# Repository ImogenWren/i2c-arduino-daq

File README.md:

# i2c Sensor Breakout Board for Data Aquisition Tasks
Flexible system for gathering i2c sensor data and providing sources to Data Aquisition software (LabVIEW, Python, Matlab, Terra Term, etc)

_The included firmware shows how to wrap up any external sensor library into a flexible format that allows easy modification to existing system and easy addition of 
new sensors._

_PCB Developed for use with Senserion i2c sensors, though is compatable with any i2c enabled periferal devices_

- Data output in CSV format over USB Serial connection as MVP for communications or logging with external software
- Could be improved by the addition of ModBus or JSON formatted data communication with error checking

## PCB

## Hardware Required
- Arduino Nano (PCB designed for this footprint, but other Arduino boards are compatable)
	- SDA A4
	- SCL A5
	
- DAQ (Data AQuisition) PCB
- Logging software
- USB port

## Sensirion SCD41 - CO2 Sensor - i2c
 - 5v or 3.3v

## Sensirion SEK-STC31 - CO2 Sensor - i2c

- 5v or 3.3v (calibrated for 3.3v)

 - Pinout: 
	- Vdd: brown    green
	- SCL: green    brown
	- GND: pink 	pink
	- SDA: yellow	Yellow
 
# Everything LabView

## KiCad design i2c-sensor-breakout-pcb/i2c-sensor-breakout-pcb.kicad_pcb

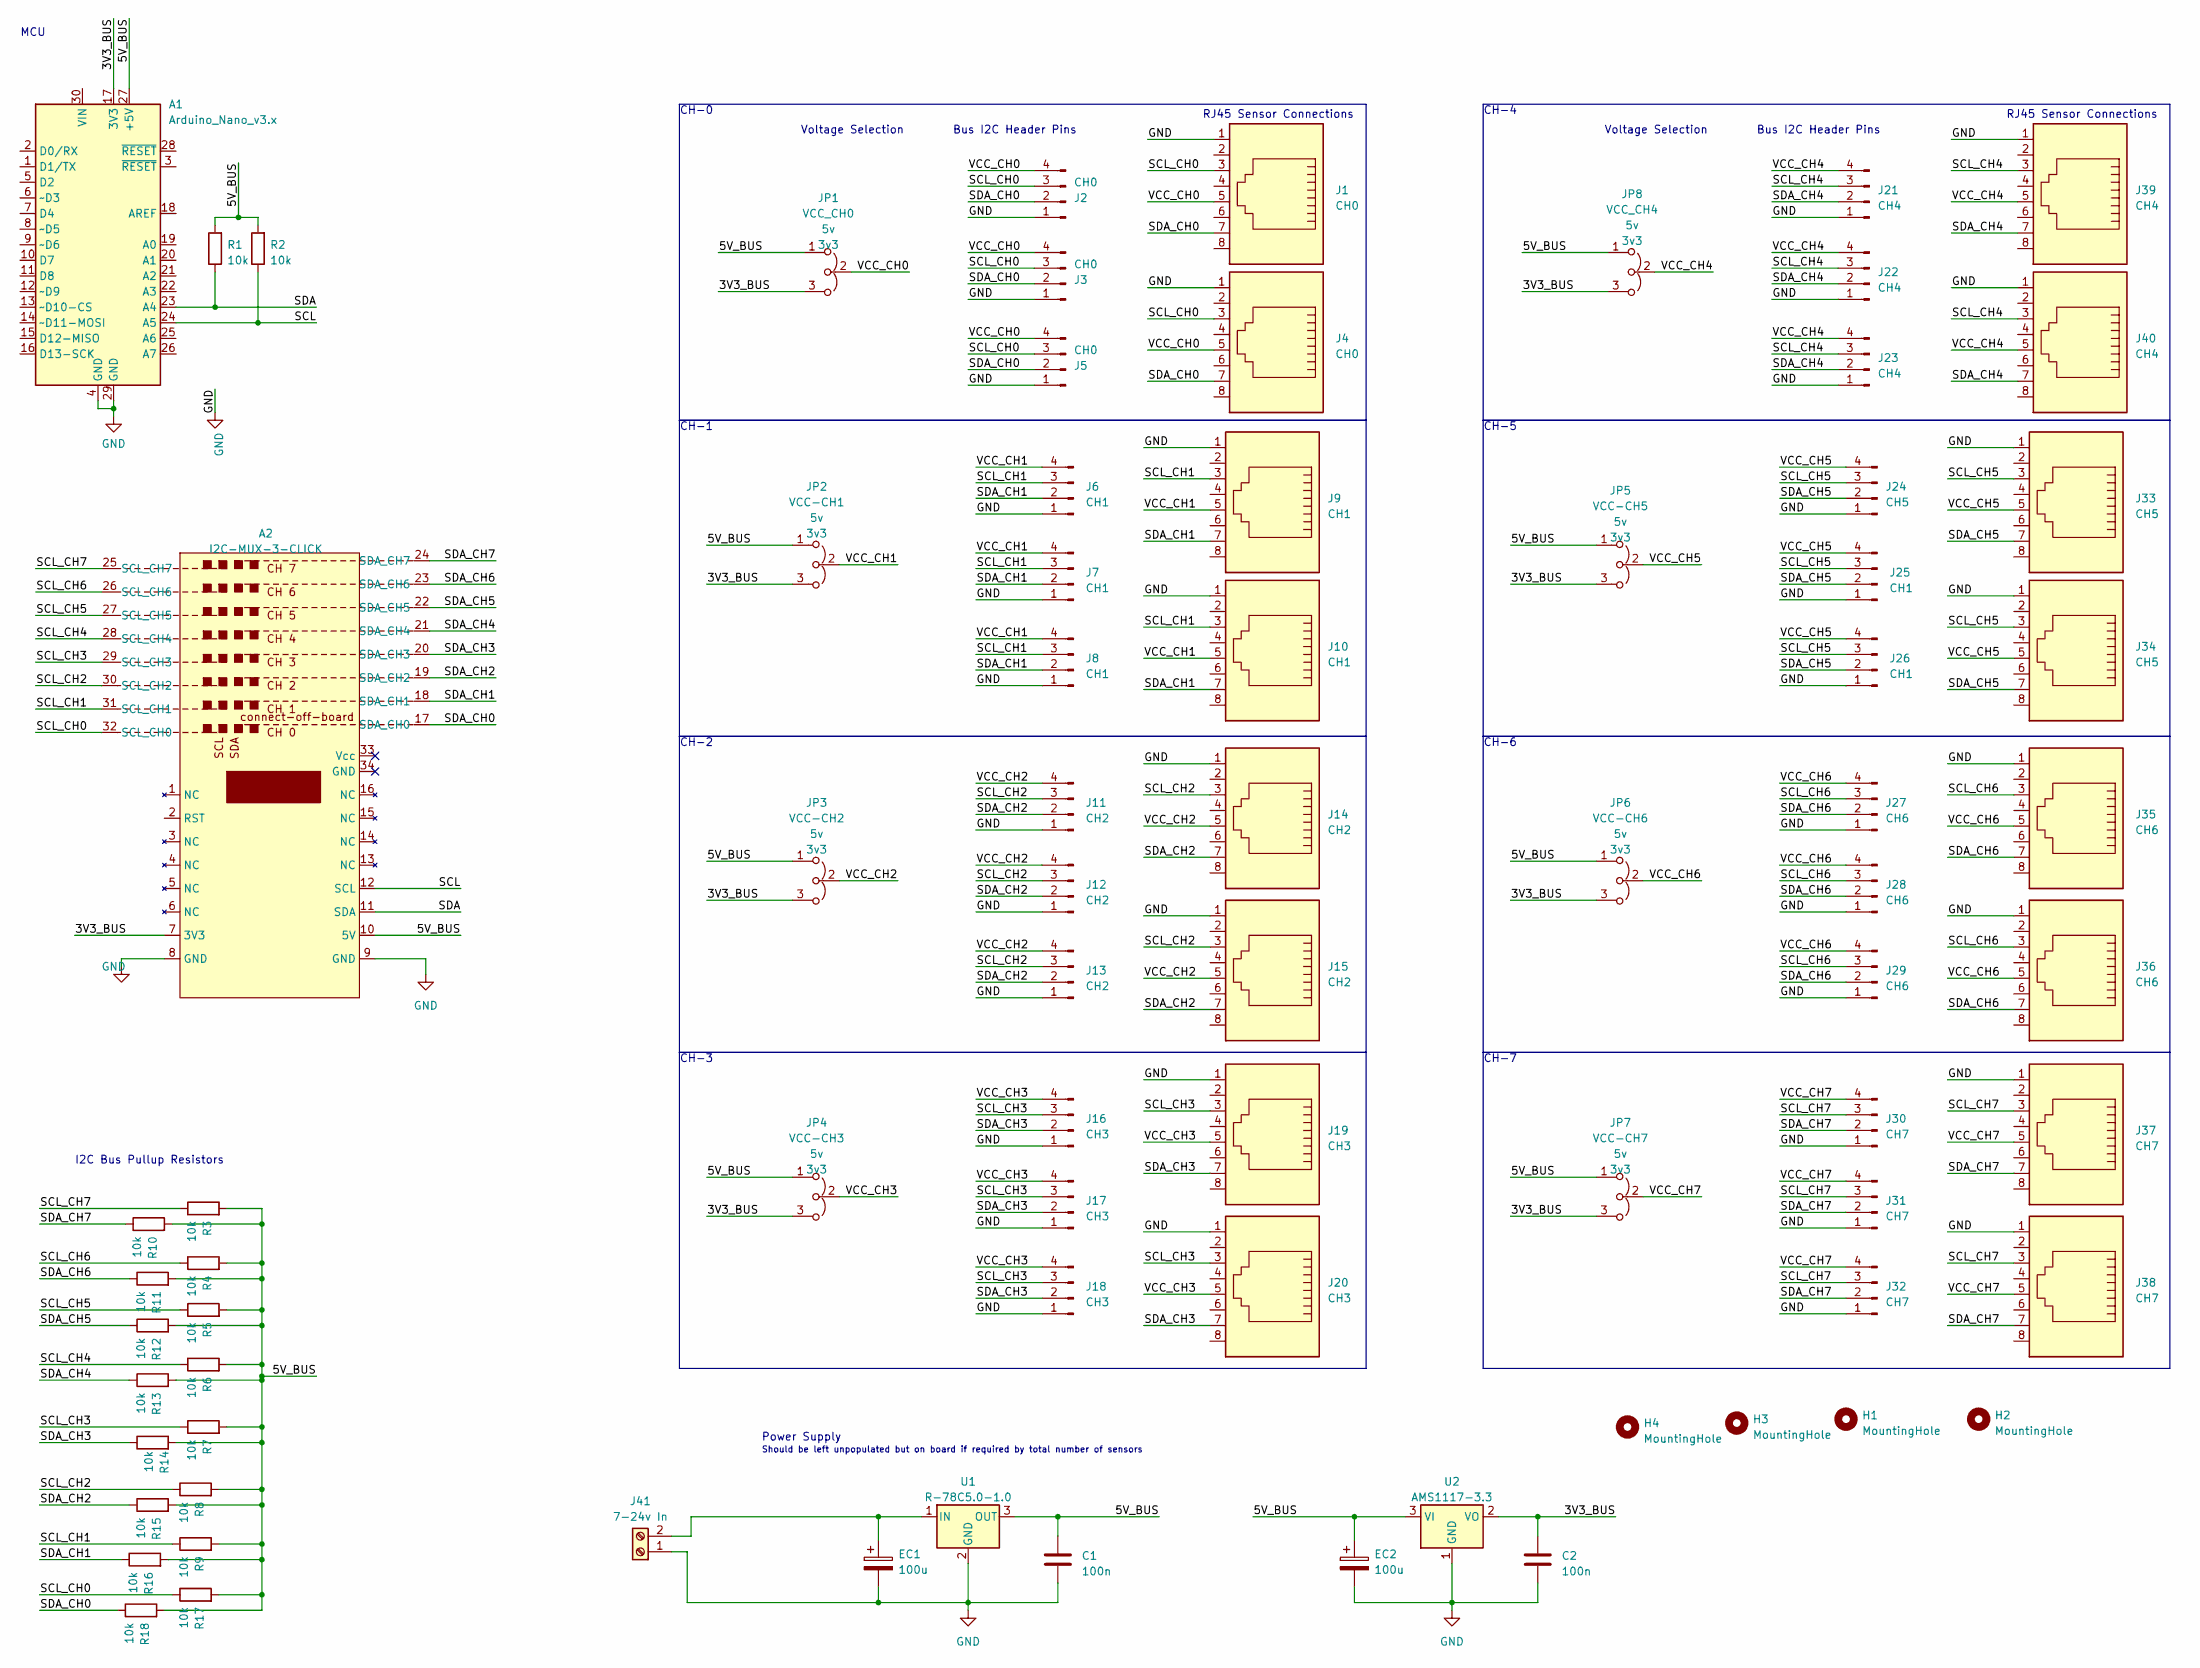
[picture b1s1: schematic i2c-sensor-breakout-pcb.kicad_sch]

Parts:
A1: Arduino_Nano_v3.x; Arduino_Nano
A2: I2C-MUX-3-CLICK
C1, C2: 100n; C_0805_2012_HandSolder_kawaii; JLCpart C779975
EC1, EC2: 100u; CP_Elec_10x10
H1, H2, H3, H4: MountingHole; MountingHole_3.2mm_M3_Pad_Via
J1, J4: CH0; RJ45_OST_PJ012-8P8CX_Vertical
J2, J3, J5: CH0; PinHeader_1x04_P2.54mm_Vertical
J6, J7, J8, J25, J26: CH1; PinHeader_1x04_P2.54mm_Vertical
J9, J10: CH1; RJ45_OST_PJ012-8P8CX_Vertical
J11, J12, J13: CH2; PinHeader_1x04_P2.54mm_Vertical
J14, J15: CH2; RJ45_OST_PJ012-8P8CX_Vertical
J16, J17, J18: CH3; PinHeader_1x04_P2.54mm_Vertical
J19, J20: CH3; RJ45_OST_PJ012-8P8CX_Vertical
J21, J22, J23: CH4; PinHeader_1x04_P2.54mm_Vertical
J24: CH5; PinHeader_1x04_P2.54mm_Vertical
J27, J28, J29: CH6; PinHeader_1x04_P2.54mm_Vertical
J30, J31, J32: CH7; PinHeader_1x04_P2.54mm_Vertical
J33, J34: CH5; RJ45_OST_PJ012-8P8CX_Vertical
J35, J36: CH6; RJ45_OST_PJ012-8P8CX_Vertical
J37, J38: CH7; RJ45_OST_PJ012-8P8CX_Vertical
J39, J40: CH4; RJ45_OST_PJ012-8P8CX_Vertical
J41: 7-24v In; TerminalBlock_Altech_AK300-2_P5.00mm; JLCpart C918120
JP1: VCC_CH0; SolderJumper-3-open-high-power
JP2: VCC-CH1; SolderJumper-3-open-high-power
JP3: VCC-CH2; SolderJumper-3-open-high-power
JP4: VCC-CH3; SolderJumper-3-open-high-power
JP5: VCC-CH5; SolderJumper-3-open-high-power
JP6: VCC-CH6; SolderJumper-3-open-high-power
JP7: VCC-CH7; SolderJumper-3-open-high-power
JP8: VCC_CH4; SolderJumper-3-open-high-power
R1, R2, R3, R4, R5, R6, R7, R8, R9, R10, R11, R12, R13, R14, R15, R16, R17, R18: 10k; R_0805_2012Metric_Pad1.20x1.40mm_HandSolder; JLCpart C2930231
U1: R-78C5.0-1.0; Converter_DCDC_RECOM_R-78E-0.5_THT
U2: AMS1117-3.3; SOT-223-3_TabPin2; JLCpart C2992570

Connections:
/3V3_BUS: A1.17 (3V3), A2.7 (3V3), C2.1, JP1.3 (B), JP2.3 (B), JP3.3 (B), JP4.3 (B), JP5.3 (B), JP6.3 (B), JP7.3 (B), JP8.3 (B), U2.2 (VO)
/5V_BUS: A1.27 (+5V), A2.10 (5V), C1.1, EC2.1, JP1.1 (A), JP2.1 (A), JP3.1 (A), JP4.1 (A), JP5.1 (A), JP6.1 (A), JP7.1 (A), JP8.1 (A), R1.2, R2.2, R3.2, R4.2, R5.2, R6.2, R7.2, R8.2, R9.2, R10.2, R11.2, R12.2, R13.2, R14.2, R15.2, R16.2, R17.2, R18.2, U1.3 (OUT), U2.3 (VI)
/SCL: A1.24 (A5), A2.12 (SCL), R2.1
/SCL_CH0: A2.32 (SCL_CH0), J1.3, J2.3, J3.3, J4.3, J5.3, R17.1
/SCL_CH1: A2.31 (SCL_CH1), J6.3, J7.3, J8.3, J9.3, J10.3, R9.1
/SCL_CH2: A2.30 (SCL_CH2), J11.3, J12.3, J13.3, J14.3, J15.3, R8.1
/SCL_CH3: A2.29 (SCL_CH3), J16.3, J17.3, J18.3, J19.3, J20.3, R7.1
/SCL_CH4: A2.28 (SCL_CH4), J21.3, J22.3, J23.3, J39.3, J40.3, R6.1
/SCL_CH5: A2.27 (SCL_CH5), J24.3, J25.3, J26.3, J33.3, J34.3, R5.1
/SCL_CH6: A2.26 (SCL_CH6), J27.3, J28.3, J29.3, J35.3, J36.3, R4.1
/SCL_CH7: A2.25 (SCL_CH7), J30.3, J31.3, J32.3, J37.3, J38.3, R3.1
/SDA: A1.23 (A4), A2.11 (SDA), R1.1
/SDA_CH0: A2.17 (SDA_CH0), J1.7, J2.2, J3.2, J4.7, J5.2, R18.1
/SDA_CH1: A2.18 (SDA_CH1), J6.2, J7.2, J8.2, J9.7, J10.7, R16.1
/SDA_CH2: A2.19 (SDA_CH2), J11.2, J12.2, J13.2, J14.7, J15.7, R15.1
/SDA_CH3: A2.20 (SDA_CH3), J16.2, J17.2, J18.2, J19.7, J20.7, R14.1
/SDA_CH4: A2.21 (SDA_CH4), J21.2, J22.2, J23.2, J39.7, J40.7, R13.1
/SDA_CH5: A2.22 (SDA_CH5), J24.2, J25.2, J26.2, J33.7, J34.7, R12.1
/SDA_CH6: A2.23 (SDA_CH6), J27.2, J28.2, J29.2, J35.7, J36.7, R11.1
/SDA_CH7: A2.24 (SDA_CH7), J30.2, J31.2, J32.2, J37.7, J38.7, R10.1
/VCC_CH0: J1.5, J2.4, J3.4, J4.5, J5.4, JP1.2 (C)
/VCC_CH1: J6.4, J7.4, J8.4, J9.5, J10.5, JP2.2 (C)
/VCC_CH2: J11.4, J12.4, J13.4, J14.5, J15.5, JP3.2 (C)
/VCC_CH3: J16.4, J17.4, J18.4, J19.5, J20.5, JP4.2 (C)
/VCC_CH4: J21.4, J22.4, J23.4, J39.5, J40.5, JP8.2 (C)
/VCC_CH5: J24.4, J25.4, J26.4, J33.5, J34.5, JP5.2 (C)
/VCC_CH6: J27.4, J28.4, J29.4, J35.5, J36.5, JP6.2 (C)
/VCC_CH7: J30.4, J31.4, J32.4, J37.5, J38.5, JP7.2 (C)
GND: A1.4 (GND), A1.29 (GND), A2.8 (GND), A2.9 (GND), C1.2, C2.2, EC1.2, EC2.2, J1.1, J2.1, J3.1, J4.1, J5.1, J6.1, J7.1, J8.1, J9.1, J10.1, J11.1, J12.1, J13.1, J14.1, J15.1, J16.1, J17.1, J18.1, J19.1, J20.1, J21.1, J22.1, J23.1, J24.1, J25.1, J26.1, J27.1, J28.1, J29.1, J30.1, J31.1, J32.1, J33.1, J34.1, J35.1, J36.1, J37.1, J38.1, J39.1, J40.1, J41.1, U1.2 (GND), U2.1 (GND)
unnamed: EC1.1, J41.2, U1.1 (IN)

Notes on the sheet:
RJ45 Sensor Connections
CH-3
I2C Bus Pullup Resistors
Bus I2C Header Pins
CH-2
Voltage Selection
CH-7
MCU
CH-1
CH-6
Should be left unpopulated but on board if required by total number of sensors
CH-4
Power Supply
CH-0
CH-5

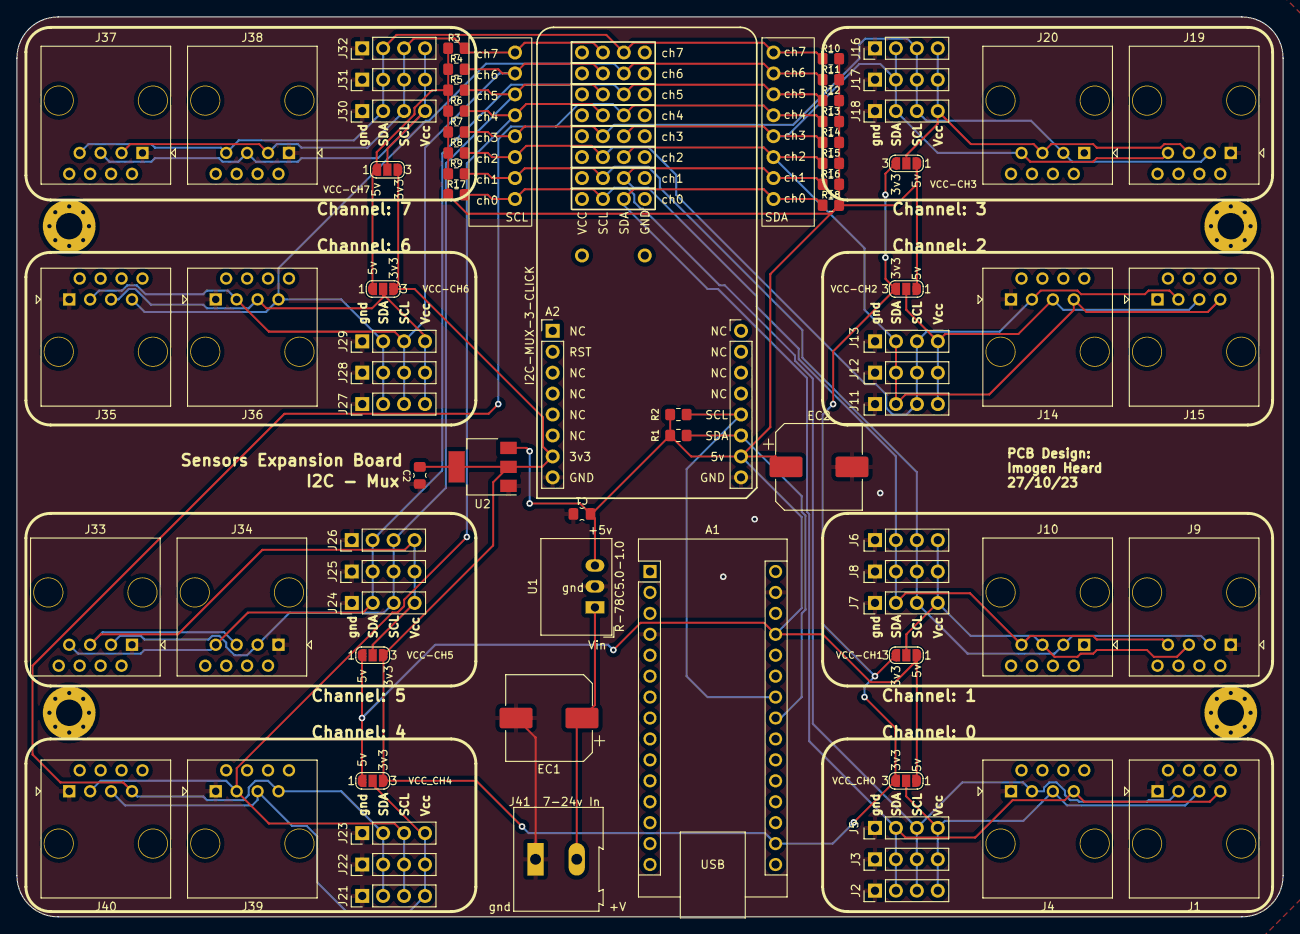
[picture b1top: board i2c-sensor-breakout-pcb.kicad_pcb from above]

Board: 2 copper layers, 153.7 x 109.2 mm, 79 parts (0 on the bottom side), 30 nets.

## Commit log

2023-09-20 jkshefjkhsfe
2023-09-21 vncfvbcdb
2023-09-22 added all types of sensor to implementation
2023-09-25 added labview stuff
2023-09-26 xcbdfgb
2023-09-27 asjkhyuoshwfhl;wefhkwegf
2023-09-28 getting i2c sensosrs working
2023-09-28 mux working, now making classes for each sensor, will improve useability
2023-09-29 dfgstarted working on main program using classes to create instances for different sensors
2023-09-29 Arduino firmware mostly completed
2023-09-29 Program mostly working #TODO: check channels for STC31s
2023-10-02 issue with not reading sensor was power related not code
2023-10-02 continued development
2023-10-26 started PCB design
2023-10-27 dfgbdfbdb
2023-10-30 PCB design Revision
2024-01-08 reorganised files
2024-01-09 simplified serial output to deal with labview bugs
2024-01-09 even more simple
2024-01-10 Removed unnessisary serial prints
2024-01-12 changed delay timings
2024-01-22 adding SDP810 differential pressure sensor
2024-01-22 working on SDP910 sensor
2024-01-22 wddgvber
2024-01-23 updated firmware to handle sdp810 differential pressure sensors
2024-01-24 Change repo to generic sensor outline
2024-01-30 updated with new implementation
